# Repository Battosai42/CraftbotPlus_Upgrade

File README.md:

# WORK IN PROGRESS!
This project is still being worked on and designs are prone to change

# Craftbot Plus Modification Purpose
The first variant of the Craftbot Plus (The one still using the drag chains) is a well built CoreXY 3D Printer, but it can no longer be considered a modern printer as it is lacking a lot of modern features and modifications are are not easy to do considering that it uses a proprietary and closed source controller board and firmware. Since this variant is using drag chains over the FFC cables, wiring to the Extruder is relatively simple to modify which opens up the possibility to modernise the printer with a modern and open controller board and firmware an add improvements to the printer as well as adding conveniance features.

# Intended Upgrades
The goal of the modifications is a high quality print (not a super fast one) and making the printer easier and more convenient to use. The following requirements list the intended upgrades and the state of implementation:

## Hardware
- [X] Duet Controller Board with external WiFi Antenna (Duet3 Mini 5+)
- [X] Filament Runout Sensor
- [X] Bed Probe (Duet3D IR Probe)
- [ ] Toolhead PCB (for easier modifications and chamber temperature sensor)
- [ ] Accelerometer (LIS3DSH)

## Software
- [X] Reprap Firmware (v 3.4)
- [X] Pressure Advance
- [X] Mesh bed compensation
- [ ] Input Shaping

## General
- [ ] Open Source wherever possible

# Instructions
TBD..

- [ ] Electronics Bay Modifications
- [ ] Duet Wiring
- [ ] Extruder
- [ ] Enclosure

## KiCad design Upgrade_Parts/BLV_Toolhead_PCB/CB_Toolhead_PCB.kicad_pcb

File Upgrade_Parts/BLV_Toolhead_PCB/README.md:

# Toolhead PCB
The toolhead PCB makes wiring and modifications on the Extruder much easier as it makes it possible to disconnect all heaters/fans sensors etc. from the wiring loom. The toolhead PCB contains connectors for all sensors and actuators on the Extruder carriage. All connectors are either of the type Molex Micro-Fit or JST.

# Supported Features
- [ ] 2x8 Molex Micro-Fit connector for wiring loom
- [ ] Heater connector for up to 70W
- [ ] Hotend thermistor/PT1000 connector
- [ ] Hotend fan connector (24V)
- [ ] Part cooling fan connector (24V)
- [ ] Duet3D IR Probe (ABL Sensor) connector
- [ ] Chamber temperature thermistor
- [ ] Extruder stepper motor connector
- [ ] Integrated x-limit switch
- [ ] Integrated accelerometer (LIS3DSH)

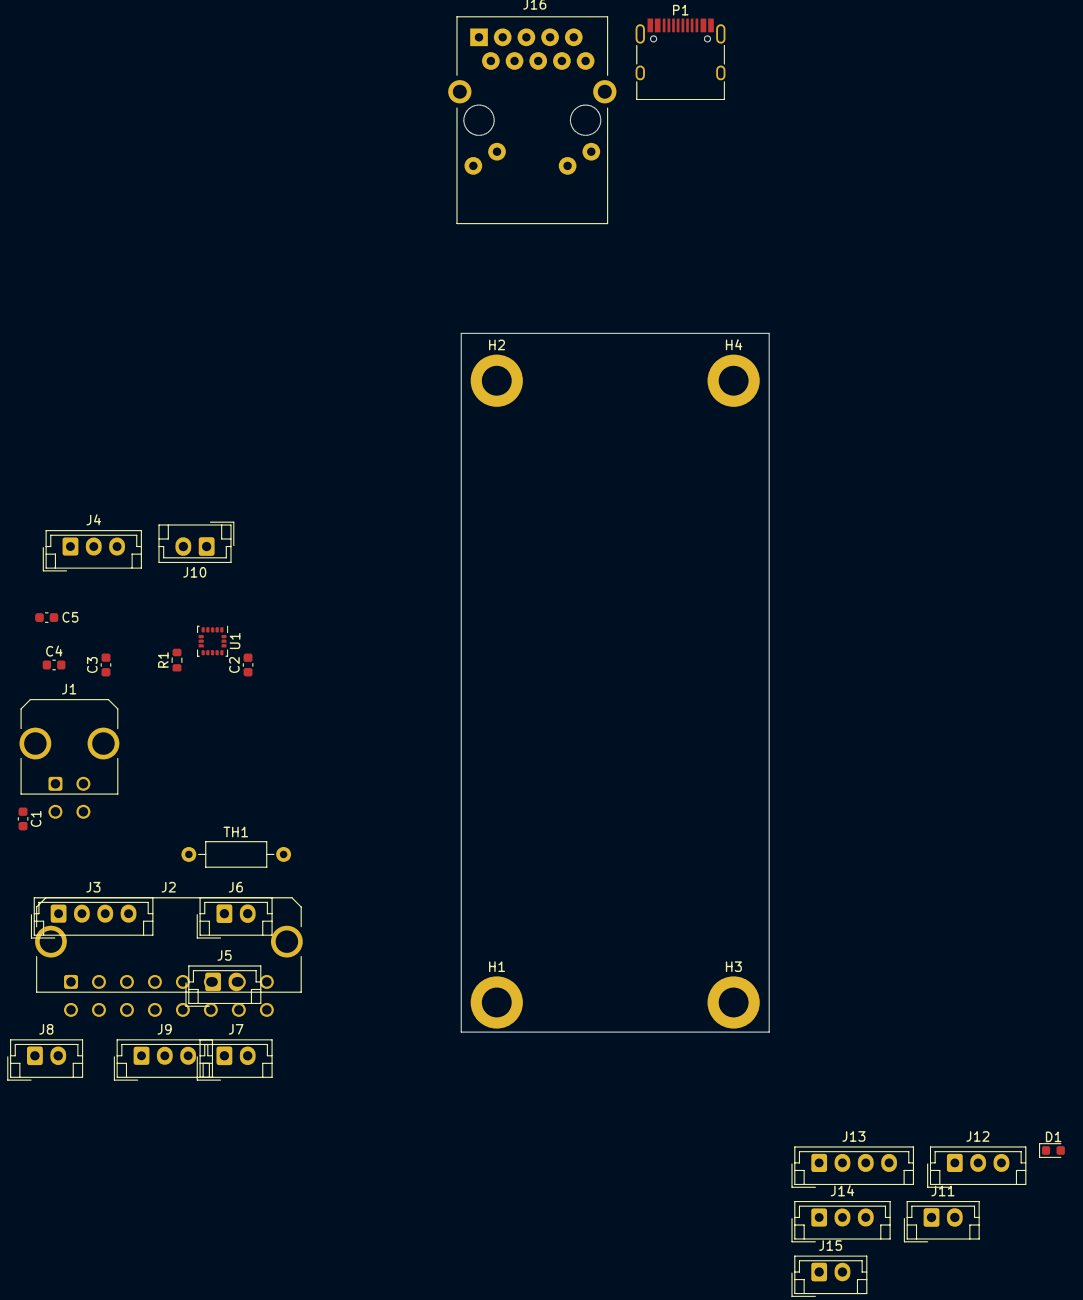
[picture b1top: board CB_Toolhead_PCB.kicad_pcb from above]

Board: 2 copper layers, 33.0 x 74.9 mm, 30 parts (0 on the bottom side), 26 nets, no tracks yet.

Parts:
C1, C2, C3, C5: 10u; C_0603_1608Metric
C4: 100n; C_0603_1608Metric
D1: BAS; D_0603_1608Metric
H1, H2, H3, H4: M3_Mount; MountingHole_3.2mm_M3_DIN965_Pad
J1: Power; Molex_Micro-Fit_3.0_43045-0421_2x02-1MP_P3.00mm_Horizontal
J2: Micro-Fit; Molex_Micro-Fit_3.0_43045-1621_2x08-1MP_P3.00mm_Horizontal
J3, J13: JST-4; JST_EH_B4B-EH-A_1x04_P2.50mm_Vertical
J4, J12, J14: JST-3; JST_EH_B3B-EH-A_1x03_P2.50mm_Vertical
J5, J6, J7, J8, J10, J11, J15: JST-2; JST_EH_B2B-EH-A_1x02_P2.50mm_Vertical
J9: Endstop; JST_EH_B3B-EH-A_1x03_P2.50mm_Vertical
J16: RB1-125B8G1A; RJ45_UDE_RB1-125B8G1A
P1: USB_C_Plug_USB2.0; USB_C_Receptacle_HRO_TYPE-C-31-M-12
R1: 470R; R_0603_1608Metric
TH1: Semitec 104GT2; R_Axial_DIN0207_L6.3mm_D2.5mm_P10.16mm_Horizontal
U1: LIS3DH; LGA-16_3x3mm_P0.5mm_LayoutBorder3x5y

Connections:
+3V3: C2.1, C4.1, C5.1, J1.1, J12.1, U1.1 (VDD_IO), U1.14 (VDD)
+5V: C3.1, J1.3, J4.1, J13.1, J14.2
+24V: C1.1, J1.2, J5.1, J6.1, J7.1, J8.1, J10.1
/1A: J2.4, J3.1
/1B: J2.6, J3.2
/2A: J2.8, J3.3
/2B: J2.10, J3.4
/Accelerometer1/INT1: J16.R8 (TD4+), P1.A6 (D+), U1.11 (INT1)
/Accelerometer1/SPI_CS: J16.R6 (TD3+), P1.A7 (D-), U1.8 (CS)
/Accelerometer1/SPI_MISO: J16.R2 (TD1+), P1.A4 (VBUS), P1.A9 (VBUS), P1.B4 (VBUS), P1.B9 (VBUS), U1.7 (SDO/SA0)
/Accelerometer1/SPI_MOSI: J16.R3 (TD1-), P1.A5 (CC), U1.6 (SDA/SDI/SDO)
/Accelerometer1/SPI_SCK: J16.R4 (TD2+), P1.B5 (VCONN), U1.4 (SCL/SPC)
/heater: J2.2, J7.2
/neopixel_do: J2.5, J8.2, R1.1
/partfan: J2.11, J5.2, J10.2
/pwm_ctrl: J2.13, J14.3
/thermistor: J2.7, J11.1
/toolfan: J2.9, J6.2
/x_endstop: J2.1, J9.1
/z_probe: D1.2 (A), J2.3, J12.2, J15.2
/z_probe_th: J2.14, J13.4
GND: C1.2, C2.2, C3.2, C4.2, C5.2, H1.1, H2.1, H3.1, H4.1, J4.3, J9.3, J13.2, J14.1, J15.1, J16.R5 (TD2-), J16.R7 (TD3-), J16.R9 (TD4-), J16.R10 (GND), J16.SH, P1.A1 (GND), P1.A12 (GND), P1.B1 (GND), P1.B12 (GND), P1.S1 (SHIELD), U1.5 (GND), U1.10 (GND), U1.12 (GND)
GNDA: J1.4, J11.2, J12.3, TH1.2
unnamed: D1.1 (K), J13.3
unnamed: J2.12, TH1.1
unnamed: J4.2, R1.2

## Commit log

2022-03-01 Update README.md
    initial project description
2022-03-01 Update README.md
    work in progress
2022-03-01 added gitignore
2022-03-01 minor toolhead pcb update
2022-03-01 remove kicad backups
2022-03-28 added model of x-carriage
2022-03-28 addet .step model for xcarriage
2022-03-29 Update README.md
    added bed probe
2022-03-29 added images
2022-03-29 Update README.md
    added image
2022-03-29 updated RRF config
2022-03-29 added readme
2022-03-29 Update README.md
    fixed image link
2022-03-29 added hotend image
2022-03-29 added slicer profile
2022-03-29 Update README.md
    fixed link
2022-03-29 Update README.md
    added more descriptions
2022-03-29 Update README.md
    added external mods
2022-04-02 added display
2022-04-02 updated display case files
2022-07-13 push latest
2022-07-13 added LIS3DH
2022-07-16 added BLV variant
2022-07-16 termination fix
2022-07-16 using 3.3V LVDS driver
2022-07-16 gitignore updated
2022-07-17 added schematic pdf
2022-07-17 added interface board
2022-07-17 added terminals
2022-07-17 cleanup
2022-07-17 replaced lvds drver
2022-07-18 new page for periphery
2022-08-03 removed lvds drivers
